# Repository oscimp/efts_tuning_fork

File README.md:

# <a href="https://efts.eu">European Frequency and Time Seminar (EFTS)</a> quartz tuning fork laboratory session.

A quartz tuning fork packaged in a transparent casing is used to demonstrate
* closed loop oscillation using a Negative Impedance Converter (NIC) circuit (<a href="oscillator/oscillateur_1night.png">Allan deviation</a> below $10^{-9}$ up to 30 s integration time).
* openloop stroboscopic imaging of the quartz prong motion driven by sound card output.

<a href=kicad/>KiCAD</a> board design files.

## References:

### Hardware (using a <a href="stroboscopy/IMG_20260409_120540_544.jpg">Raspberry Pi5</a> single board computer for running GNU Radio for controlling the sound card and recording the video stream):
* 32768 Hz tuning fork in transparent package: <a href="https://eu.mouser.com/ProductDetail/Epson-Timing/FC-135-32.7680KA-AC5?qs=f9yNj16SXrLM6nHs1T34rQ%3D%3D">Epson FC-135 32.7680KA-AC5</a> (0.404 euros/p)
* sound card with sampling rate 96 kHz or higher, e.g. <a href="https://www.amazon.fr/-/en/UGREEN-External-Headphones-Compatible-Raspberry/dp/B08Y8CZB2S/">UGREEN (10.2 euros on amazon)</a> although a <a href="http://www.thomann.fr/focusrite_scarlett_solo_3rd_gen.htm">Focusrite Scarlett Solo</a>
(89 euros but 192 kS/s at 24 bits) might be a wiser choice if can be afforded (see <a href="stroboscopy/">bottom of this page</a>).
* "digital microscope" webcam, e.g. <a href="https://amscope.co.uk/products/c-hhd510-w">AmScope HHD Series</a> (~50 euros)
* 7414 Schmitt trigger (0.5 to 0.7 euros)
* 7400 NAND gate (0.2 to 0.3 euros)

**Note**: the single board computer **must** be a RPi5 and **not** a RPi4 whose USB bus is too unstable to generate a clean audio signal probing
the narrow tuning fork resonance. See the <a href="stroboscopy">stroboscopy</a> subdirectory for the demonstration.

### Software

* use ``mplayer tv://`` to display the webcam output (or ``vlc`` if it displays properly in the
selected window manager): allows for stretching the image to full screen even if recording a "poor" 
webcam resolution (640x480) stream from the digital microscope.
* GNU Radio <a href="stroboscopy/snd.grc">flowchart</a> for driving the two channels of the
stereo sound card (tested with GNU Radio 3.10) with 1 Hz offset between the signal driving
the tuning fork and the stroboscopic signal driving the LED.
* Maybe wise to ``echo "performance" > /sys/devices/system/cpu/cpu0/cpufreq/scaling_governor`` 
to run the CPUs at maximum speed (will heat to 65 degC).

## Resources:

Equivalent BvD model of the quartz tuning fork (see <a href="KeysightE4990A/">the impedance analyzer</a> measurement):
* R1=53727 $\Omega$
* L1=7221 H
* C1=3.268 fF
* C0=3.368 pF

Quality factor $Q=\frac{1}{R1}\sqrt{\frac{L1}{C1}}=27700$

Resonance frequency $f=\frac{1}{2\pi\sqrt{L1\cdot C1}}=\frac{1}{2\pi\sqrt{7221\times 3.268\cdot 10^{-15}}}=32763$ Hz

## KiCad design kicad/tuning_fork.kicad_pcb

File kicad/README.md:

# KiCAD schematic and board design files.

The non-plated through holes have been placed with a spacing compatible with
installing the board on top of a Raspberry Pi 4/5 single board computer for
a compact setup. Whether the heat dissipated by the processor will affect
the resonator performance remains to be demonstrated.

The potentiometer closest to the audio input aims at adding a DC offset to bring
the audio output within the range of the Schmitt trigger toggling voltage. Set
the sound card output to maximum amplitude to increase chances of the Schmitt 
trigger toggling. The potentiometer further from the audio input is the negative
impedance and should be tuned so that the oscillator starts (slowly !) at resonance
frequency of the tuning fork.

The setup is designed to be assembled on a Rapsberry Pi 4/5:

## Schematic

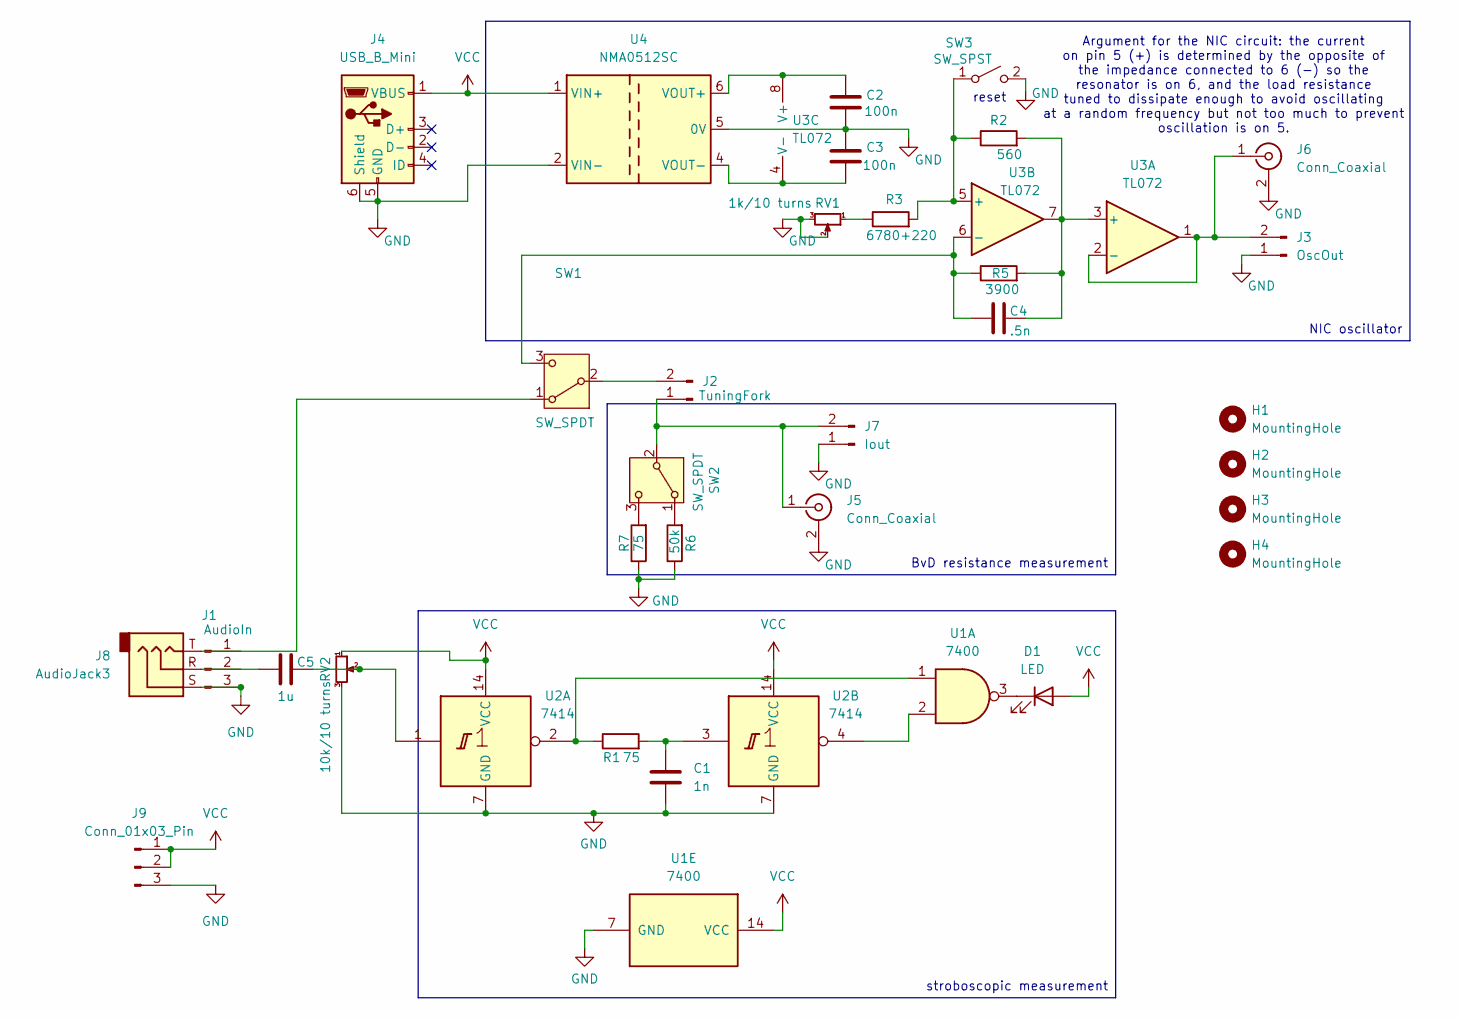
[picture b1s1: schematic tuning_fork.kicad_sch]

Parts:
C1: 1n; C_Rect_L7.0mm_W3.5mm_P5.00mm
C2, C3: 100n; C_0805_2012Metric_Pad1.18x1.45mm_HandSolder
C4: .5n; C_Rect_L7.0mm_W2.0mm_P5.00mm
C5: 1u; C_Rect_L7.0mm_W2.0mm_P5.00mm
D1: LED; LED_D3.0mm
H1, H2, H3, H4: MountingHole; MountingHole_3.2mm_M3
J1: AudioIn; PinHeader_1x03_P2.54mm_Vertical
J2: TuningFork; PinHeader_1x02_P2.54mm_Vertical
J3: OscOut; PinHeader_1x02_P2.54mm_Vertical
J4: USB_B_Mini; USB_Mini-B_Lumberg_2486_01_Horizontal
J5, J6: Conn_Coaxial; SMA_Molex_73251-1153_EdgeMount_Horizontal
J7: Iout; PinHeader_1x02_P2.54mm_Vertical
J8: AudioJack3; Jack_3.5mm_Lumberg_1503_02_Horizontal
J9: Conn_01x03_Pin; PinSocket_1x03_P2.54mm_Vertical
R1: 75; R_Axial_DIN0204_L3.6mm_D1.6mm_P2.54mm_Vertical
R2: 560; R_Axial_DIN0204_L3.6mm_D1.6mm_P7.62mm_Horizontal
R3: 6780+220; R_Axial_DIN0204_L3.6mm_D1.6mm_P7.62mm_Horizontal
R5: 3900; R_Axial_DIN0204_L3.6mm_D1.6mm_P7.62mm_Horizontal
R6: 50k; R_Axial_DIN0204_L3.6mm_D1.6mm_P7.62mm_Horizontal
R7: 75; R_Axial_DIN0204_L3.6mm_D1.6mm_P7.62mm_Horizontal
RV1: 1k/10 turns; Potentiometer_Bourns_3296W_Vertical
RV2: 10k/10 turns; Potentiometer_Bourns_3296W_Vertical
SW1, SW2: SW_SPDT; SW_Slide-03_Wuerth-WS-SLTV_10x2.5x6.4_P2.54mm
SW3: SW_SPST; SW_TH_Tactile_Omron_B3F-100x
U1: 7400; DIP-14_W7.62mm
U2: 7414; DIP-14_W7.62mm
U3: TL072; DIP-8_W7.62mm_Socket
U4: NMA0512SC; Converter_DCDC_Murata_NMAxxxxSC_THT

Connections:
GND: C1.2, C2.2, C3.1, J1.3 (Pin_3_3), J3.1, J4.5 (GND), J4.6 (Shield), J5.2 (Ext), J6.2 (Ext), J7.1, J8.S, J9.3, R6.1, R7.1, RV1.2, RV1.3, RV2.3, SW3.2 (B), U1.7 (GND), U2.7 (GND), U4.2 (VIN-), U4.5 (0V)
unnamed: C1.1, R1.2, U2.3
unnamed: C5.1, J8.R
unnamed: C5.2, RV2.2, U2.1
unnamed: D1.1 (K), U1.3
unnamed: J2.1, J5.1 (In), J7.2, SW2.2 (B)
unnamed: J2.2, SW1.2 (B)
unnamed: J3.2, J6.1 (In), U3.1, U3.2 (-)
unnamed: R1.1, U1.1, U2.2
unnamed: R3.1, RV1.1
unnamed: J8.T, SW1.1 (A)
unnamed: C4.1, R5.1, SW1.3 (C), U3.6 (-)
unnamed: R6.2, SW2.1 (A)
unnamed: R7.2, SW2.3 (C)
unnamed: R2.1, R3.2, SW3.1 (A), U3.5 (+)
unnamed: U1.2, U2.4
unnamed: C4.2, R2.2, R5.2, U3.3 (+), U3.7
unnamed: C2.1, U3.8 (V+), U4.6 (VOUT+)
unnamed: C3.2, U3.4 (V-), U4.4 (VOUT-)
VCC: D1.2 (A), J4.1 (VBUS), J9.1, J9.2, RV2.1, U1.14 (VCC), U2.14 (VCC), U4.1 (VIN+)

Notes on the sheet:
reset
Argument for the NIC circuit: the current on pin 5 (+) is determined by the opposite of the impedance connected to 6 (-) so the resonator is on 6, and the load resistance tuned to dissipate enough to avoid oscillating at a random frequency but not too much to prevent oscillation is on 5.
stroboscopic measurement
BvD resistance measurement
NIC oscillator

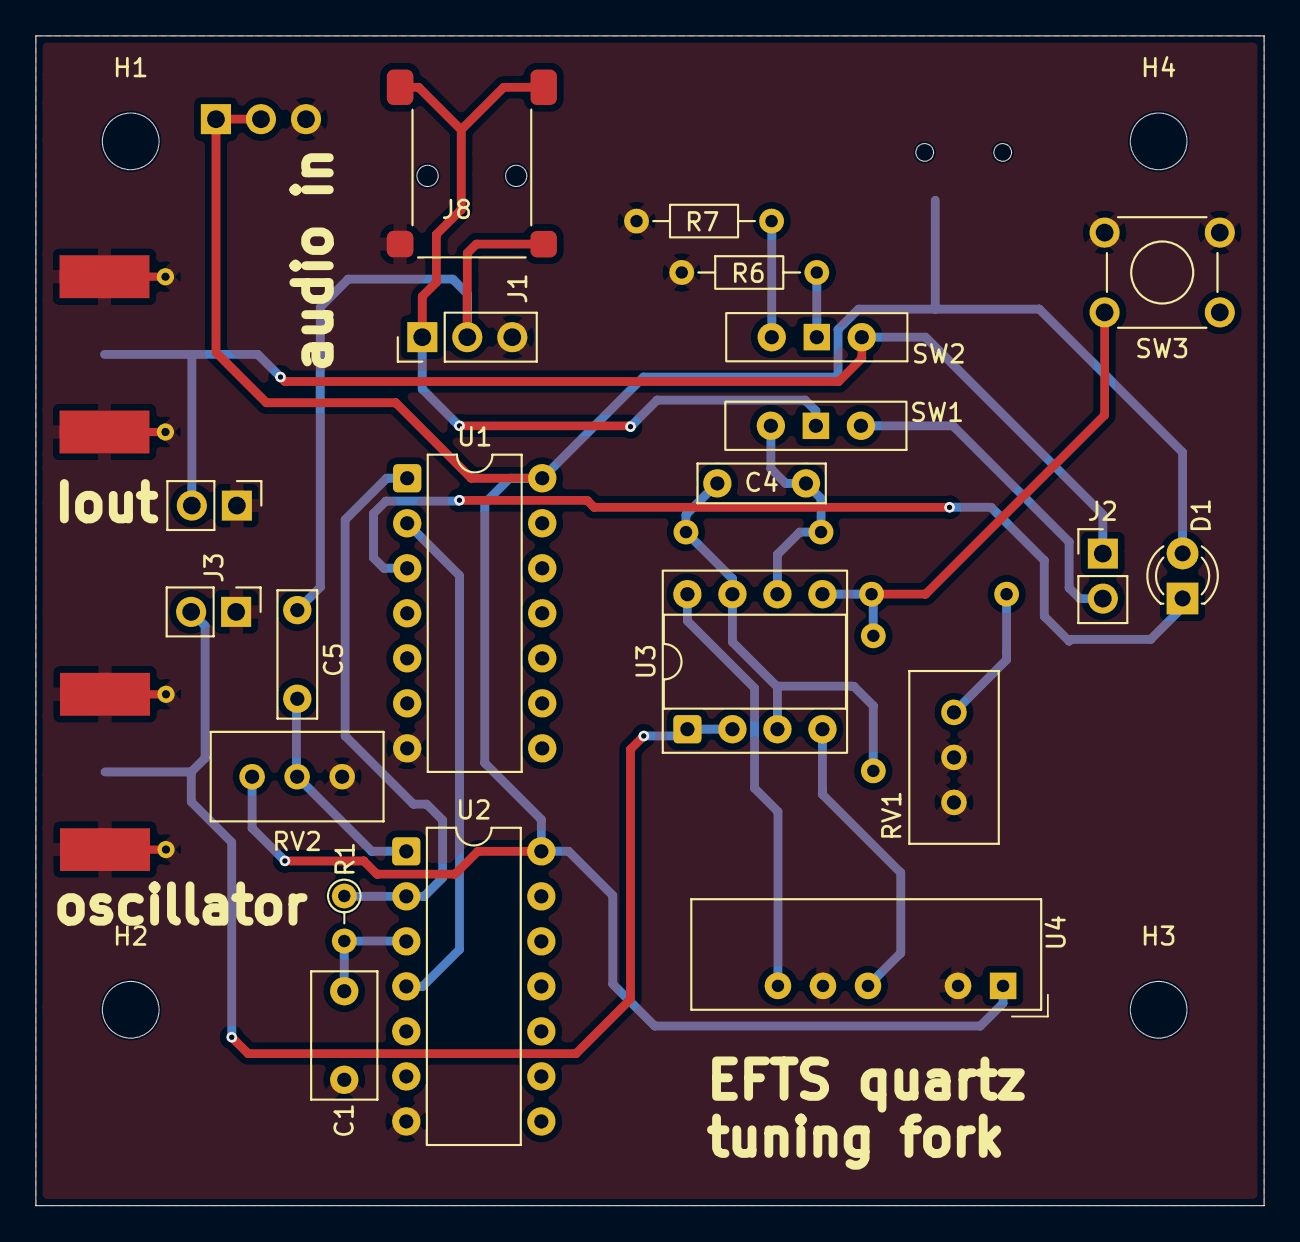
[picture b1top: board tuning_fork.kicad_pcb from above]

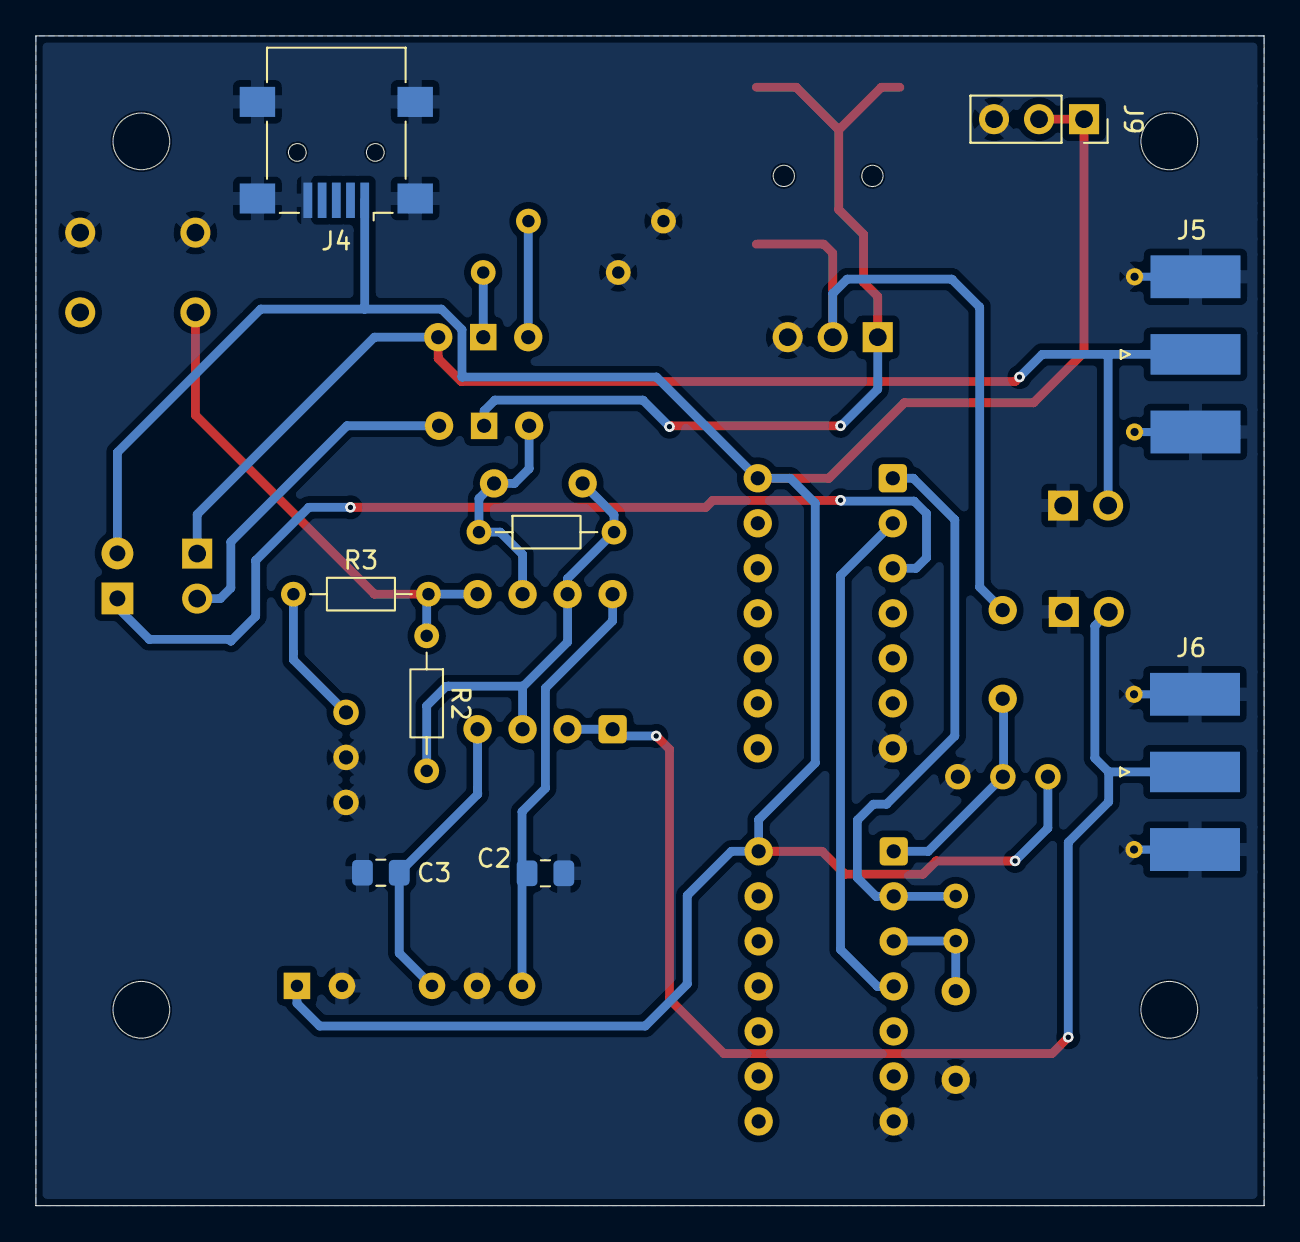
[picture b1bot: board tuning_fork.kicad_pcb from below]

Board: 2 copper layers, 69.3 x 66.0 mm, 34 parts (9 on the bottom side), 20 nets.

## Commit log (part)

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2026-04-09 tuning fork reference & BvD
2026-04-09 hardware decription
2026-04-09 Allan
2026-04-10 move mounthing holes to RPi5 location
2026-04-10 kicad
2026-04-10 allan description
2026-04-14 improved layout for usability
2026-05-12 RPi5
2026-05-21 add RPi +5V supply header
2026-06-05 syllabus
2026-06-05 improve layout
2026-06-05 add schematic PNG and PDF
2026-06-06 first functional setup
2026-06-06 functional oscillator
2026-06-09 add oscillator reset push button
2026-06-10 add impedance analyzer measurement
2026-06-16 image + remove capa if the oscillator fails to start
2026-06-19 cross correlation processing script
2026-06-24 CPU performance
2026-06-26 startup time
2026-06-26 ref biblio
2026-06-26 demonstration
2026-06-27 screenshots of RPi sound output through the tuning fork
2026-06-27 update screenshot
